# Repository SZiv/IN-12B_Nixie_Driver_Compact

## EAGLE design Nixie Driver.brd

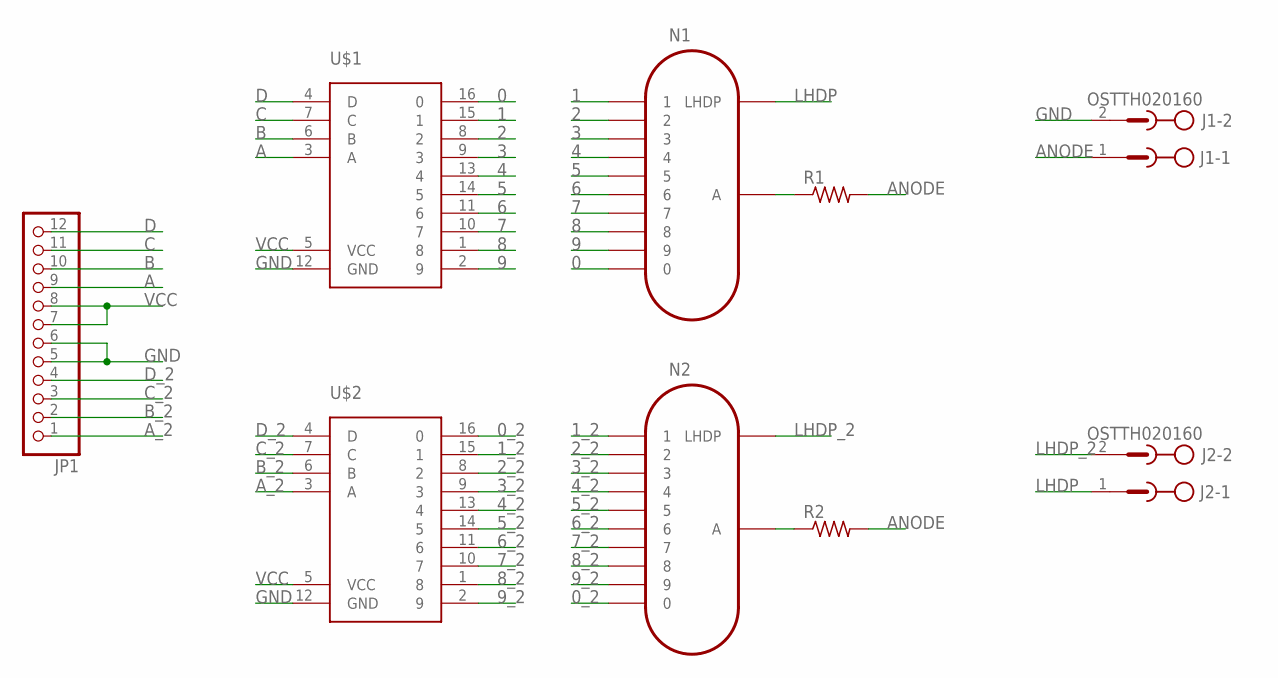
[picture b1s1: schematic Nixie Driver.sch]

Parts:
J1, J2: OSTTH020160; EDSTL130-02
JP1: PINHD-1X12-CB; 1X12-CB
N1, N2: IN-12B; IN-12
R1, R2: R-US_0204/7; 0204/7
U$1, U$2: K155ID1; DIL16-KIT

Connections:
0: N1.0, U$1.16 (0)
0_2: N2.0, U$2.16 (0)
1: N1.1, U$1.15 (1)
1_2: N2.1, U$2.15 (1)
2: N1.2, U$1.8 (2)
2_2: N2.2, U$2.8 (2)
3: N1.3, U$1.9 (3)
3_2: N2.3, U$2.9 (3)
4: N1.4, U$1.13 (4)
4_2: N2.4, U$2.13 (4)
5: N1.5, U$1.14 (5)
5_2: N2.5, U$2.14 (5)
6: N1.6, U$1.11 (6)
6_2: N2.6, U$2.11 (6)
7: N1.7, U$1.10 (7)
7_2: N2.7, U$2.10 (7)
8: N1.8, U$1.1 (8)
8_2: N2.8, U$2.1 (8)
9: N1.9, U$1.2 (9)
9_2: N2.9, U$2.2 (9)
A: JP1.9, U$1.3 (A)
ANODE: J1.1, R1.2, R2.2
A_2: JP1.1, U$2.3 (A)
B: JP1.10, U$1.6 (B)
B_2: JP1.2, U$2.6 (B)
C: JP1.11, U$1.7 (C)
C_2: JP1.3, U$2.7 (C)
D: JP1.12, U$1.4 (D)
D_2: JP1.4, U$2.4 (D)
GND: J1.2, JP1.5, JP1.6, U$1.12 (GND), U$2.12 (GND)
LHDP: J2.1, N1.LHDP
LHDP_2: J2.2, N2.LHDP
unnamed: N1.A, R1.1
unnamed: N2.A, R2.1
VCC: JP1.7, JP1.8, U$1.5 (VCC), U$2.5 (VCC)

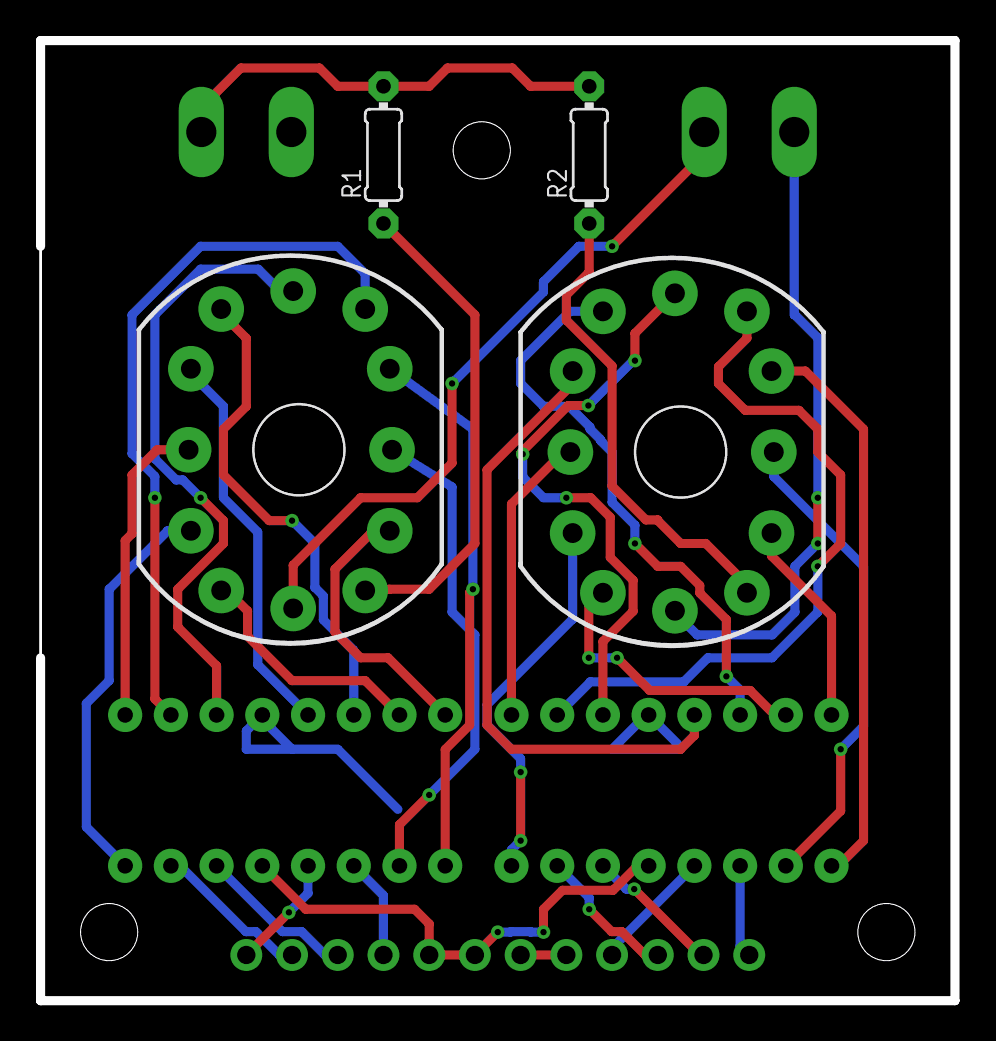
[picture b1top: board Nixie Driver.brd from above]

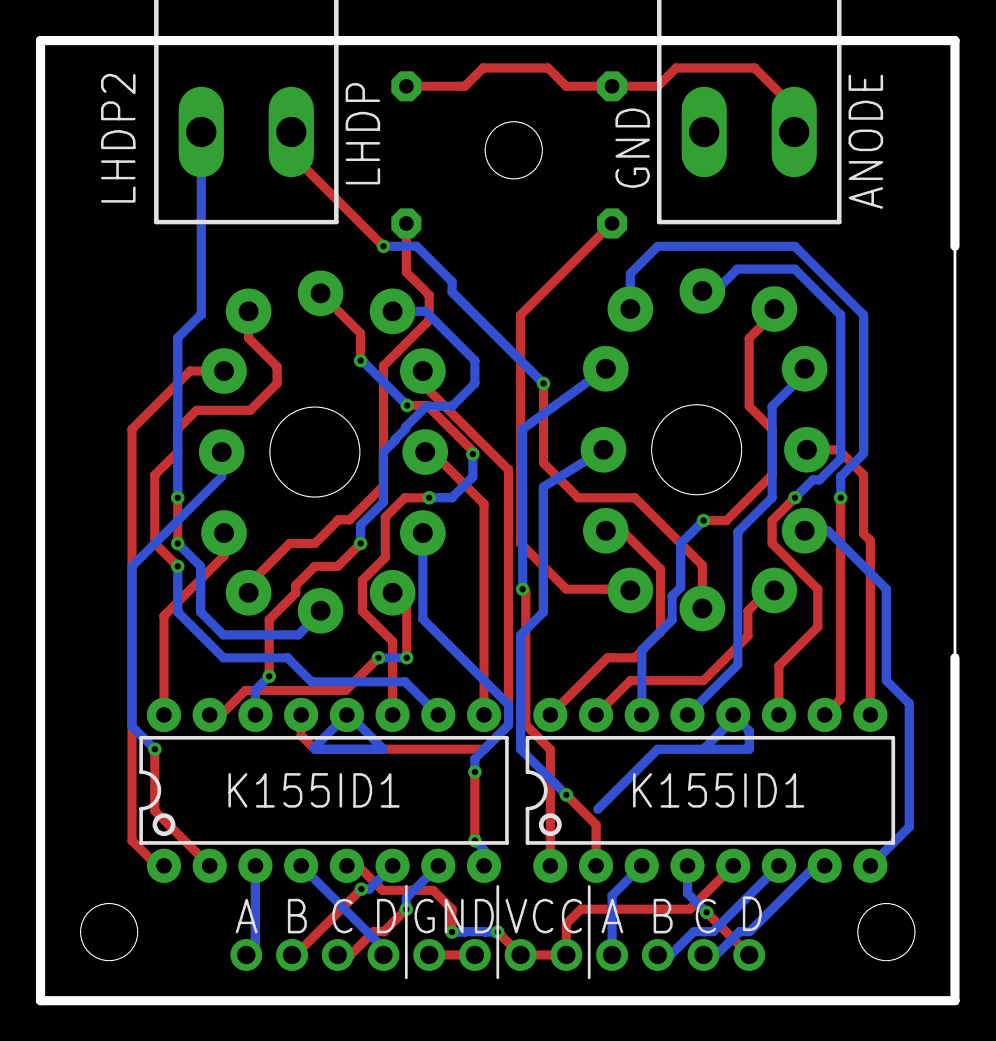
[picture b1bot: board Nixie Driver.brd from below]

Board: 2 copper layers, 50.8 x 53.3 mm, 9 parts (4 on the bottom side), 35 nets.

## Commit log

2017-11-19 :circus_tent: Added .gitattributes & .gitignore files
2017-11-19 First Commit!
    First Commit!

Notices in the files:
parts and their libraries:
con-ost: Copyright (C) 2008, Bob Starr
